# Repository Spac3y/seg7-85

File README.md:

# seg7-85

A 4-digit 7-segment display driven by an ATtiny85, scrolling a text message across the display.

## How it works

The ATtiny85 bit-bangs two daisy-chained 74HC595 shift registers to drive a common-anode 4-digit 7-segment display (segments + digit select). A Timer1 CTC interrupt (~3 Hz) shifts the next character of the message into a 4-character rolling buffer, which is refreshed continuously via multiplexing.

## Hardware (BOM)

| Ref | Part | Qty |
|-----|------|-----|
| U1 | ATtiny85 (DIP-8) | 1 |
| U3, U4 | 74HC595 shift register (DIP-16) | 2 |
| U2 | 4-digit 7-segment display (CC56-12SURKWA) | 1 |
| R1–R4 | 220Ω (segment current limiting) | 4 |
| R5 | 10kΩ (reset pull-up) | 1 |
| C1–C3 | 10µF decoupling | 3 |
| SW1 | Push button (reset/mode) | 1 |
| J1 | 1x06 pin header | 1 |
| J2 | Molex KK-254 1x02 power connector | 1 |

Full BOM: [`kicad/attiny85_7seg.csv`](kicad/attiny85_7seg.csv)

## Repo layout

- `attiny-85_code/attiny-85_code.ino` — firmware (Arduino/AVR)
- `kicad/` — KiCad schematic, PCB layout, and design files
- `kicad/changes.md` — schematic/PCB change log

## Pinout (ATtiny85)

| Pin | Function |
|-----|----------|
| PB0 | Shift register data (SER/DS) |
| PB2 | Shift register clock (SRCLK/SHCP) |
| PB3 | Shift register latch (RCLK/STCP) |
| PB4 | Shift register reset (SRCLR/MR) |

## Building/flashing

Flash `attiny-85_code.ino` to the ATtiny85 using the Arduino IDE with an [ATtiny core](https://github.com/SpenceKonde/ATTinyCore) installed, via ISP.

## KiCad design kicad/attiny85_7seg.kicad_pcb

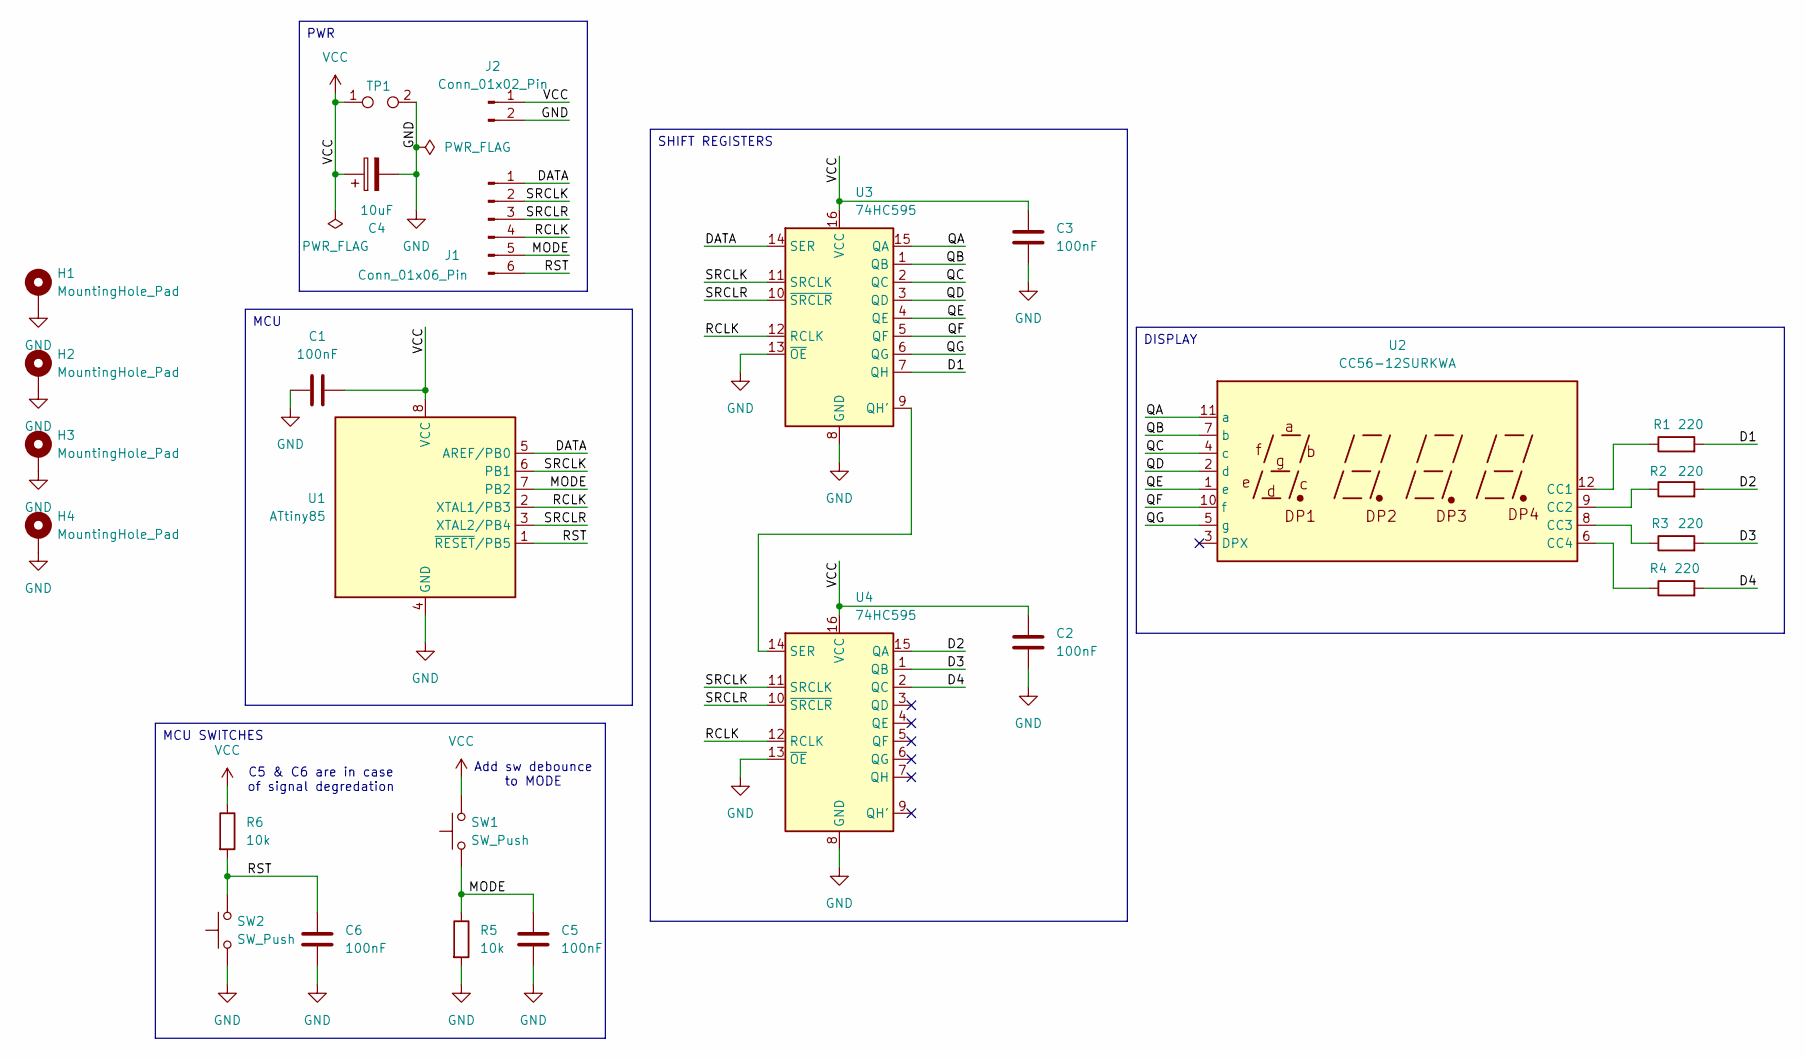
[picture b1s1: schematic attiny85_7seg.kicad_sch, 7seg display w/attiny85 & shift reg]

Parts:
C1, C2, C3, C5, C6: 100nF; C_Disc_D10.0mm_W2.5mm_P5.00mm
C4: 10uF; CP_Radial_D5.0mm_P2.50mm
H1, H2, H3, H4: MountingHole_Pad; MountingHole_2.7mm_M2.5_DIN965_Pad_TopBottom
J1: Conn_01x06_Pin; PinHeader_2x03_P2.54mm_Vertical
J2: Conn_01x02_Pin; Molex_KK-254_AE-6410-02A_1x02_P2.54mm_Vertical
R1, R2, R3, R4: 220; R_Axial_DIN0207_L6.3mm_D2.5mm_P10.16mm_Horizontal
R5, R6: 10k; R_Axial_DIN0207_L6.3mm_D2.5mm_P10.16mm_Horizontal
SW1, SW2: SW_Push; SW_PUSH_6mm
TP1: TestPoint_2Pole; TestPoint_2Pads_Pitch2.54mm_Drill0.8mm
U1: ATtiny85; DIP-8_W7.62mm
U2: CC56-12SURKWA; CA56-12SURKWA
U3, U4: 74HC595; DIP-16_W7.62mm

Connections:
/D1: R1.2, U3.7 (QH)
/D2: R2.2, U4.15 (QA)
/D3: R3.2, U4.1 (QB)
/D4: R4.2, U4.2 (QC)
/DATA: J1.1, U1.5 (AREF/PB0), U3.14 (SER)
/MODE: C5.1, J1.5, R5.1, SW1.1, U1.7 (PB2)
/QA: U2.11 (a), U3.15 (QA)
/QB: U2.7 (b), U3.1 (QB)
/QC: U2.4 (c), U3.2 (QC)
/QD: U2.2 (d), U3.3 (QD)
/QE: U2.1 (e), U3.4 (QE)
/QF: U2.10 (f), U3.5 (QF)
/QG: U2.5 (g), U3.6 (QG)
/RCLK: J1.4, U1.2 (XTAL1/PB3), U3.12 (RCLK), U4.12 (RCLK)
/RST: C6.1, J1.6, R6.2, SW2.2, U1.1 (~RESET/PB5)
/SRCLK: J1.2, U1.6 (PB1), U3.11 (SRCLK), U4.11 (SRCLK)
/SRCLR: J1.3, U1.3 (XTAL2/PB4), U3.10 (~SRCLR), U4.10 (~SRCLR)
GND: C1.1, C2.2, C3.2, C4.2, C5.2, C6.2, H1.1 (1_1), H2.1 (1_1), H3.1 (1_1), H4.1 (1_1), J2.2, R5.2, SW2.1, TP1.2, U1.4 (GND), U3.8 (GND), U3.13 (~OE), U4.8 (GND), U4.13 (~OE)
unnamed: R1.1, U2.12 (CC1)
unnamed: R2.1, U2.9 (CC2)
unnamed: R3.1, U2.8 (CC3)
unnamed: R4.1, U2.6 (CC4)
unnamed: U3.9 (QH'), U4.14 (SER)
VCC: C1.2, C2.1, C3.1, C4.1, J2.1, R6.1, SW1.2, TP1.1, U1.8 (VCC), U3.16 (VCC), U4.16 (VCC)

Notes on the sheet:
C5 & C6 are in case of signal degredation
Add sw debounce to MODE
SHIFT REGISTERS
DISPLAY
PWR
MCU
MCU SWITCHES

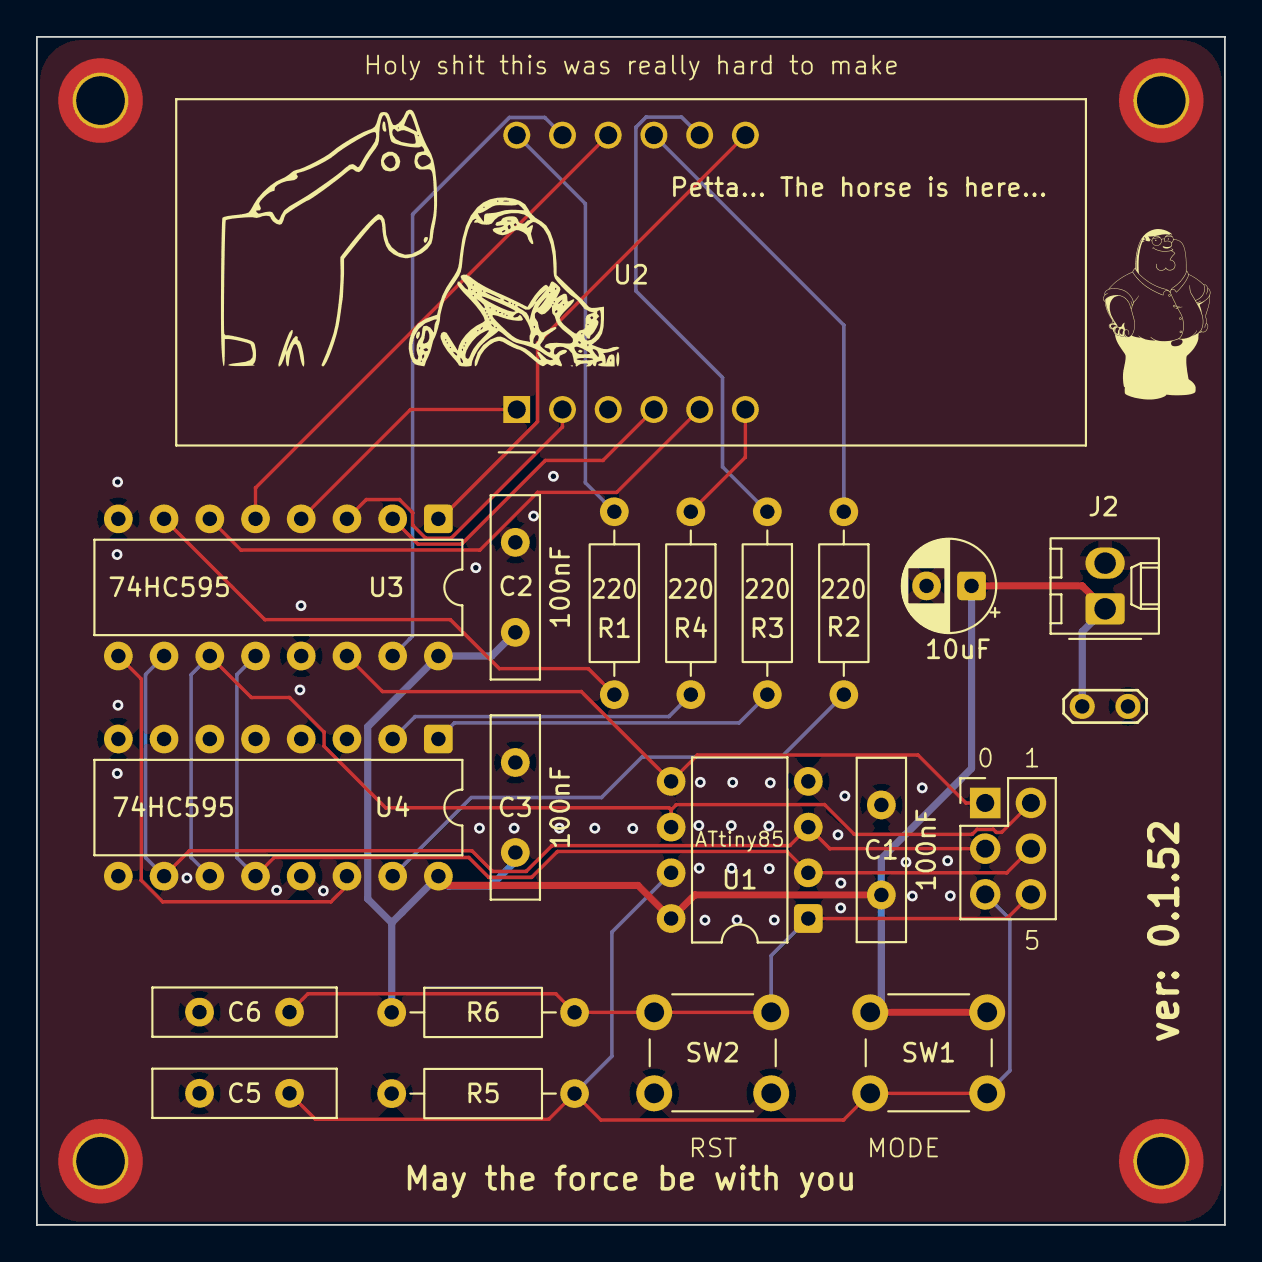
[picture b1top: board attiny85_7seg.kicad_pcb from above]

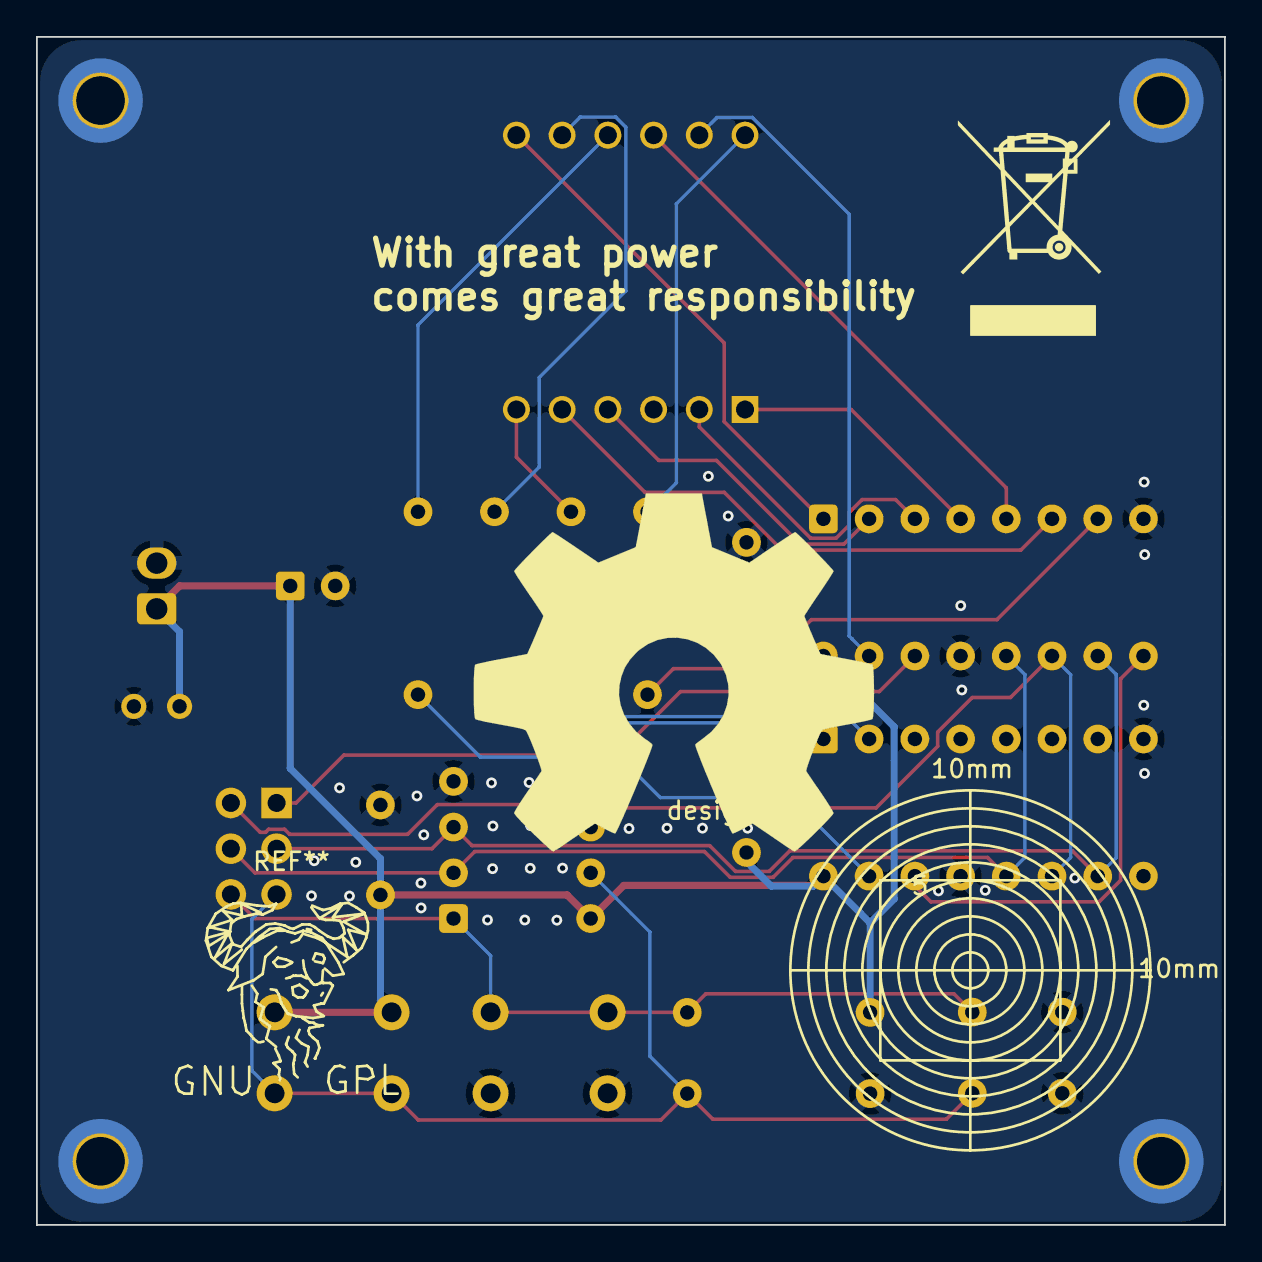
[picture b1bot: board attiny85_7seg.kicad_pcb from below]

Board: 2 copper layers, 66.0 x 66.0 mm, 29 parts (2 on the bottom side), 24 nets.

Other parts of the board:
IMG1: LOGO; Peter_Image
IMG3: WEEE-Logo_8.4x12mm_SilkScreen
LOGO1: LOGO; thehorseishere
design1: Gauge_10mm_Type3_SilkScreenTop

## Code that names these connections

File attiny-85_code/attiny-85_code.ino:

#define DATA_PIN 0   // PB0 - SER   (DS)
#define CLOCK_PIN 1  // PB2 - SRCLK (SHCP)  ← moved from PB1
#define RESET_PIN 2  // PB4 - SRCLR (MR)    ← moved from PB3
#define LATCH_PIN 3  // PB3 - RCLK  (STCP)  ← moved from PB2

// ATtiny85 Timer1: 8-bit, prescaler /16384
// 8MHz / 16384 / 162 ≈ 3 Hz scroll rate
#define TIMER1_TOP 162

const size_t segLen = 7;
const size_t digitsLen = 4;

const char keys[] = { 'I', 'L', 'O', 'V', 'E', 'Y', 'U', 'H', ' ', '-' };
const uint8_t values[] = { 0b0000110, 0b0001110, 0b1111110, 0b0111110, 0b1001111, 0b0110011, 0b0111110, 0b0110111, 0b0000000, 0b0000001 };
const uint8_t MAP_SIZE = 10;


const char message[] = "I LOVE YOU   ";
const uint16_t length = sizeof(message) / sizeof(message[0]);

volatile unsigned ind = 0;
volatile char buffer[4] = { ' ', ' ', ' ', ' ' };
/* 3    2    1    0*/
volatile bool doShift = false;

uint8_t getMapValue(char key) {
  for (uint8_t i = 0; i < MAP_SIZE; i++)
    if (keys[i] == key)
      return values[i];
  return 0;
}

void resetShiftRegister() {
  digitalWrite(RESET_PIN, LOW);
  delayMicroseconds(1);
  digitalWrite(RESET_PIN, HIGH);
}

void latchOutput() {
  digitalWrite(LATCH_PIN, HIGH);
  delayMicroseconds(1);
  digitalWrite(LATCH_PIN, LOW);
}

uint16_t combineData(uint8_t data, uint8_t poz) {
  poz = ~(1 << poz);
  uint16_t rez = ((uint16_t)(data & 0x7F) << 4) | (poz & 0x0F);
  return rez;
}

void writeShiftRegister(uint8_t data, uint8_t poz) {
  // 1. Clear shift register before writing
  resetShiftRegister();

  uint16_t value = combineData(data, poz);

  // 2. Clock out 11 bits, MSB first
  for (int8_t bit = 0; bit < 11; bit++) {
    digitalWrite(DATA_PIN, (value >> bit) & 0x01);
    digitalWrite(CLOCK_PIN, HIGH);
    delayMicroseconds(1);
    digitalWrite(CLOCK_PIN, LOW);
  }

  // 3. Transfer shift register → output latches
  latchOutput();
}

void displayBuffer() {
  for (unsigned i = 0; i < 4; i++) {
    writeShiftRegister(getMapValue(buffer[i]), 3 - i);
    delay(2);
  }
}

void shiftLetter(char letter) {
  for (unsigned i = 1; i < 4; i++) {
    buffer[i - 1] = buffer[i];
  }
  buffer[3] = letter;
}

ISR(TIMER1_COMPA_vect) {
  doShift = true;
}

void startAnimation() {
  const unsigned frameTime = 125;   // how long each frame should stay visible
  const unsigned refreshDelay = 2;  // per-digit refresh time, as before
  const unsigned sweeps = frameTime / (4 * refreshDelay);

  // Segment chase across all 4 digits
  for (short i = 0; i < 7; i++) {
    uint8_t data = ~(1 << i) & 0x7F;
    for (unsigned s = 0; s < sweeps; s++) {
      for (short j = 0; j < 4; j++) {
        writeShiftRegister(data, j);
        delay(refreshDelay);
      }
    }
  }

  // Blink "----" three times
  for (short i = 0; i < 3; i++) {
    for (unsigned s = 0; s < sweeps; s++) {
      for (short j = 0; j < 4; j++) {
        writeShiftRegister(getMapValue('-'), j);
        delay(refreshDelay);
      }
    }
    for (unsigned s = 0; s < sweeps; s++) {
      for (short j = 0; j < 4; j++) {
        writeShiftRegister(getMapValue(' '), j);
        delay(refreshDelay);
      }
    }
  }
}

void setup() {

  pinMode(DATA_PIN, OUTPUT);
  pinMode(CLOCK_PIN, OUTPUT);
  pinMode(LATCH_PIN, OUTPUT);
  pinMode(RESET_PIN, OUTPUT);

  resetShiftRegister();

  startAnimation();

  cli();
  TCCR1 = 0;
  GTCCR = 0;
  TCNT1 = 0;
  OCR1C = TIMER1_TOP;      // TOP for CTC mode
  OCR1A = TIMER1_TOP;      // compare match A = fire ISR at TOP
  TCCR1 |= (1 << CTC1);    // CTC mode (clear on OCR1C match)
  TCCR1 |= 0x0F;           // prescaler /16384 (CS13:CS10 = 1111)
  TIMSK |= (1 << OCIE1A);  // enable compare match A interrupt
  sei();
}

void loop() {
  if (doShift) {
    doShift = false;
    shiftLetter(message[ind]);
    ind = (ind + 1) % length;
  }
  displayBuffer();
}

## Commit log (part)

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2026-06-05 v1.2.0
2026-06-09 0.0.3
2026-06-10 0.0.4
2026-06-11 0.0.41
2026-06-15 v0.0.5
2026-06-27 v0.0.6
